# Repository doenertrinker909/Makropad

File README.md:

# Makropad

A minimalistic makropad featuring a 4x4 grid of keys, two rotary encoders and a 128x32 OLED display. 

You can put most makropad-like keyboards in two categories:

Way too expensive and overbloated with useless features

or

An ok price but an ugly design (in my opinion)

That's what motivated me to make my own makropad. It's designed to be easily built, having just the right amount of features all while having a sleek minimalistic design.

# Features

- Arduino Pro Micro MCU (ATmega32u4)
- Two customizable rotary encoders
- A 128x32 OLED that displays helpful information
- Custom shortcuts for any program (with QMK)
- Power via USB-C
- Sleek minimalistic case optimised for CNC milling and 3D printing
- Hot swap switches

# PCB

The pcb layout

<details>
  <summary> The schematics </summary>
  
  The MCU with the encoders and OLED

  The switch matrix

  The LED matrix

</details>

# First start

- By default the makropad will work like a standard numpad in the following format:

<kbd> 7 </kbd> <kbd> 8 </kbd> <kbd> 9 </kbd> <kbd> + </kbd>

<kbd> 4 </kbd> <kbd> 5 </kbd> <kbd> 6 </kbd> <kbd> - </kbd>

<kbd> 1 </kbd> <kbd> 2 </kbd> <kbd> 3 </kbd> <kbd> * </kbd>

<kbd> 0 </kbd> <kbd> . </kbd> <kbd> / </kbd> <kbd> ↵ </kbd>

- You can either just compile and flash the firmware with QMK toolbox or choose to customize the code further to your needs
- By customizing the QMK files you can make it your own

# BOM

This is an estimated cost:
| Product Name            | Product Description            | Product Link                                                                                              | Product Unit Cost in EUR   | Product Amount   |    Total in EUR |
|:------------------------|:-------------------------------|:----------------------------------------------------------------------------------------------------------|:---------------------------|:-----------------|----------------:|
| 1N4148WS                | Diode SOD-323                         | https://jlcpcb.com/partdetail/2485-1N4148WS/C2128                                                         | 0.0079                     | 16.0             |            0.13 |
| -                       | 128x32 OLED                    | https://www.amazon.de/-/en/gp/product/B07BDFXFRK                                                          | 4.5                        | 1.0              |            4.5  |
| WS2812B-V5/W            | LED 5050                    | https://jlcpcb.com/partdetail/Worldsemi-WS2812B_V5W/C2874885                                              | 0.09                       | 16.0             |            1.34 |
| RCA02330RJLF            | 330 Ohm resistor 0402          | https://jlcpcb.com/partdetail/23789673-RCA02330RJLF/C22356229                                             | 0.0003                     | 1.0              |            0    |
| CHERRY MX2A-71NN        | Cherry style keyboardswitch    | https://www.reichelt.de/de/de/shop/produkt/cherry_mx_silent_red_-_tastenmodul_-_schnappbefestigung-361531 | 0.75                       | 16.0             |           12    |
| -                       | EC11 Rotary encoder            | https://www.amazon.de/-/en/gp/product/B08728PS6N                                                          | 2.0                        | 2.0              |            4    |
| ARD PRO-MICRO-C         | Arduino Pro Micro (ATmega32u4) | https://www.reichelt.de/de/de/shop/produkt/arduino_-_mikrocontroller_atmega32u4_usb-c-421607              | 7.99                       | 1.0              |            7.99 |
| YMDK Kailh CPG151101S11 | Kailh Hotswap Sockets          | https://www.amazon.de/-/en/YMDK-CPG151101S11-Swappable-Mechanical-Keyboards/dp/B07K8CCMQZ                 | 0.16                       | 16.0             |            2.56 |
|                         |                                |                                                                                                           |                            |                  |           32.52 |

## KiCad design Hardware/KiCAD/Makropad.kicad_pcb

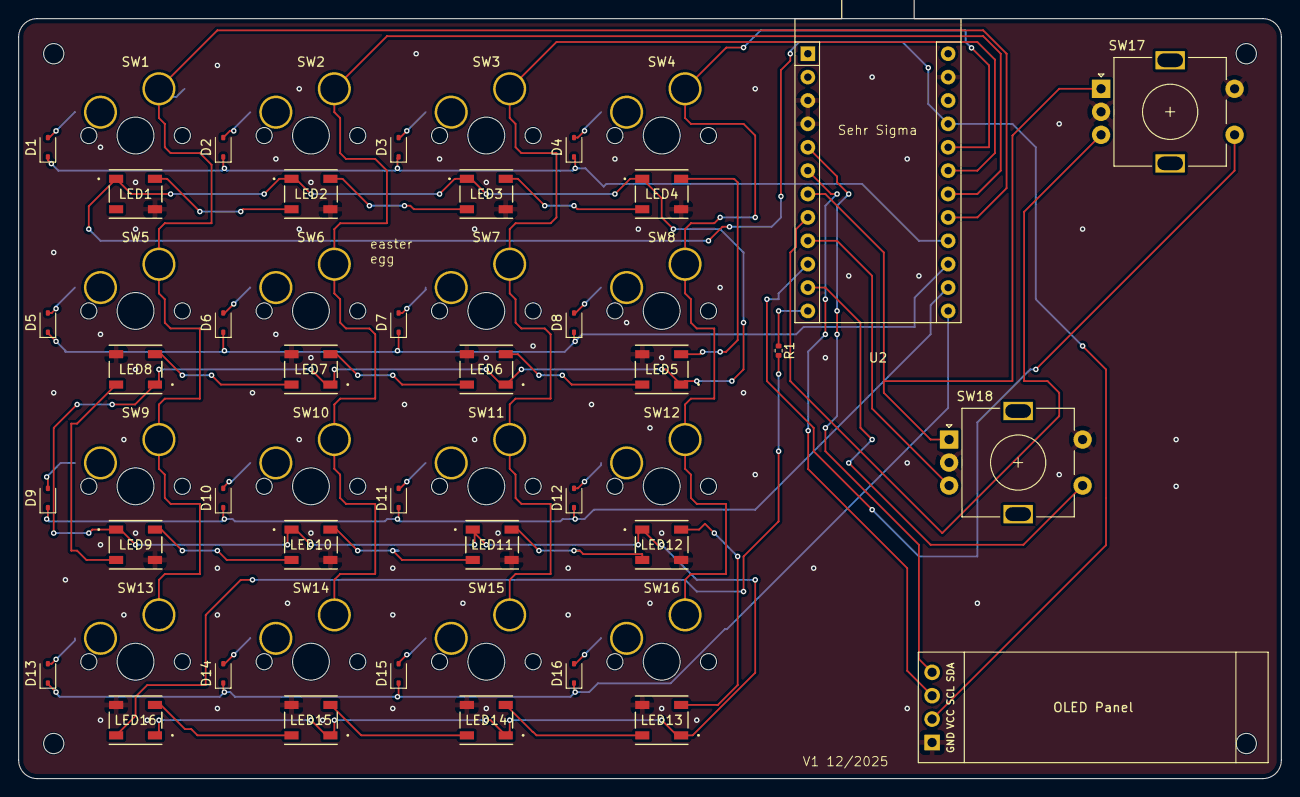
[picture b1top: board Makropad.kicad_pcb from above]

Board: 2 copper layers, 137.2 x 82.6 mm, 53 parts (0 on the bottom side), 50 nets.

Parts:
D1, D2, D3, D4, D5, D6, D7, D8, D9, D10, D11, D12, D13, D14, D15, D16: D; D_SOD-323
J1: OLED; SSD1306-0.91-OLED-4pin-128x32
LED1, LED2, LED3, LED4, LED5, LED6, LED7, LED8, LED9, LED10, LED11, LED12, LED13, LED14, LED15, LED16: WS2812B-V5/W; SMD4_LED_SMD5050_WS2812B_WDS
R1: 330; R_0402_1005Metric
SW1, SW2, SW3, SW4, SW5, SW6, SW7, SW8, SW9, SW10, SW11, SW12, SW13, SW14, SW15, SW16: SW_Push; SW_Hotswap_Kailh_MX_Plated_1.00u
SW17, SW18: RotaryEncoder_Switch; RotaryEncoder_Alps_EC11E-Switch_Vertical_H20mm
U2: Sparkfun_Pro_Micro

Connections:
+5V: J1.2, LED1.1 (VDD), LED2.1 (VDD), LED3.1 (VDD), LED4.1 (VDD), LED5.1 (VDD), LED6.1 (VDD), LED7.1 (VDD), LED8.1 (VDD), LED9.1 (VDD), LED10.1 (VDD), LED11.1 (VDD), LED12.1 (VDD), LED13.1 (VDD), LED14.1 (VDD), LED15.1 (VDD), LED16.1 (VDD), U2.21 (VCC)
A SW17: SW17.A, SW18.A, U2.7 (D4/A6)
B SW17: SW17.B, U2.8 (~D5)
B SW18: SW18.B, U2.9 (~D6/A7)
GND: J1.1, LED1.3 (VSS), LED2.3 (VSS), LED3.3 (VSS), LED4.3 (VSS), LED5.3 (VSS), LED6.3 (VSS), LED7.3 (VSS), LED8.3 (VSS), LED9.3 (VSS), LED10.3 (VSS), LED11.3 (VSS), LED12.3 (VSS), LED13.3 (VSS), LED14.3 (VSS), LED15.3 (VSS), LED16.3 (VSS), SW17.C, SW17.S2, SW18.C, SW18.S2, U2.3 (GND), U2.4 (GND), U2.23 (GND)
LED_Data: R1.1, U2.12 (~D9/A9)
unnamed: D1.2 (A), SW1.1
unnamed: D2.2 (A), SW2.1
unnamed: D3.2 (A), SW3.1
unnamed: D4.2 (A), SW4.1
unnamed: D5.2 (A), SW5.1
unnamed: D6.2 (A), SW6.1
unnamed: D7.2 (A), SW7.1
unnamed: D8.2 (A), SW8.1
unnamed: D9.2 (A), SW9.1
unnamed: D10.2 (A), SW10.1
unnamed: D11.2 (A), SW11.1
unnamed: D12.2 (A), SW12.1
unnamed: D13.2 (A), SW13.1
unnamed: D14.2 (A), SW14.1
unnamed: D15.2 (A), SW15.1
unnamed: D16.2 (A), SW16.1
unnamed: LED1.4 (DIN), LED2.2 (DOUT)
unnamed: LED2.4 (DIN), LED3.2 (DOUT)
unnamed: LED3.4 (DIN), LED4.2 (DOUT)
unnamed: LED4.4 (DIN), LED5.2 (DOUT)
unnamed: LED5.4 (DIN), LED6.2 (DOUT)
unnamed: LED6.4 (DIN), LED7.2 (DOUT)
unnamed: LED7.4 (DIN), LED8.2 (DOUT)
unnamed: LED8.4 (DIN), LED9.2 (DOUT)
unnamed: LED10.4 (DIN), LED11.2 (DOUT)
unnamed: LED9.4 (DIN), LED10.2 (DOUT)
unnamed: LED11.4 (DIN), LED12.2 (DOUT)
unnamed: LED12.4 (DIN), LED13.2 (DOUT)
unnamed: LED13.4 (DIN), LED14.2 (DOUT)
unnamed: LED14.4 (DIN), LED15.2 (DOUT)
unnamed: LED15.4 (DIN), LED16.2 (DOUT)
unnamed: LED16.4 (DIN), R1.2
S SW17: SW17.S1, U2.10 (D7)
S SW18: SW18.S1, U2.11 (D8/A8)
SCL: J1.3, U2.6 (~D3)
SDA: J1.4, U2.5 (D2)
c1: SW1.2, SW5.2, SW9.2, SW13.2, U2.17 (D18/A0)
c2: SW2.2, SW6.2, SW10.2, SW14.2, U2.18 (D19/A1)
c3: SW3.2, SW7.2, SW11.2, SW15.2, U2.19 (D20/A2)
c4: SW4.2, SW8.2, SW12.2, SW16.2, U2.20 (D21/A3)
r1: D1.1 (K), D2.1 (K), D3.1 (K), D4.1 (K), U2.16 (D15)
r2: D5.1 (K), D6.1 (K), D7.1 (K), D8.1 (K), U2.15 (D14)
r3: D9.1 (K), D10.1 (K), D11.1 (K), D12.1 (K), U2.14 (D16)
r4: D13.1 (K), D14.1 (K), D15.1 (K), D16.1 (K), U2.13 (~D10/A10)

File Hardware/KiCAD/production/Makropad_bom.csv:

Designator,Footprint,Quantity,Value,LCSC Part #
"D1, D10, D11, D12, D13, D14, D15, D16, D2, D3, D4, D5, D6, D7, D8, D9",D_SOD-323,16,D,
J1,SSD1306-0.91-OLED-4pin-128x32,1,OLED,
"LED1, LED10, LED11, LED12, LED13, LED14, LED15, LED16, LED2, LED3, LED4, LED5, LED6, LED7, LED8, LED9",SMD4_LED_SMD5050_WS2812B_WDS,16,WS2812B-V5/W,
R1,0402,1,330,
"SW1, SW10, SW11, SW12, SW13, SW14, SW15, SW16, SW2, SW3, SW4, SW5, SW6, SW7, SW8, SW9",SW_Hotswap_Kailh_MX_Plated_1.00u,16,SW_Push,
"SW17, SW18",RotaryEncoder_Alps_EC11E-Switch_Vertical_H20mm,2,RotaryEncoder_Switch,
U2,Sparkfun_Pro_Micro,1,Sparkfun_Pro_Micro,

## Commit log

2026-05-08 oled not working properly yet
2026-05-08 Fusion Files
